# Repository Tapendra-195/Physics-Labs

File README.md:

# Physics-Labs
Contains files related to work done as Department Technician at The University of Winnipeg

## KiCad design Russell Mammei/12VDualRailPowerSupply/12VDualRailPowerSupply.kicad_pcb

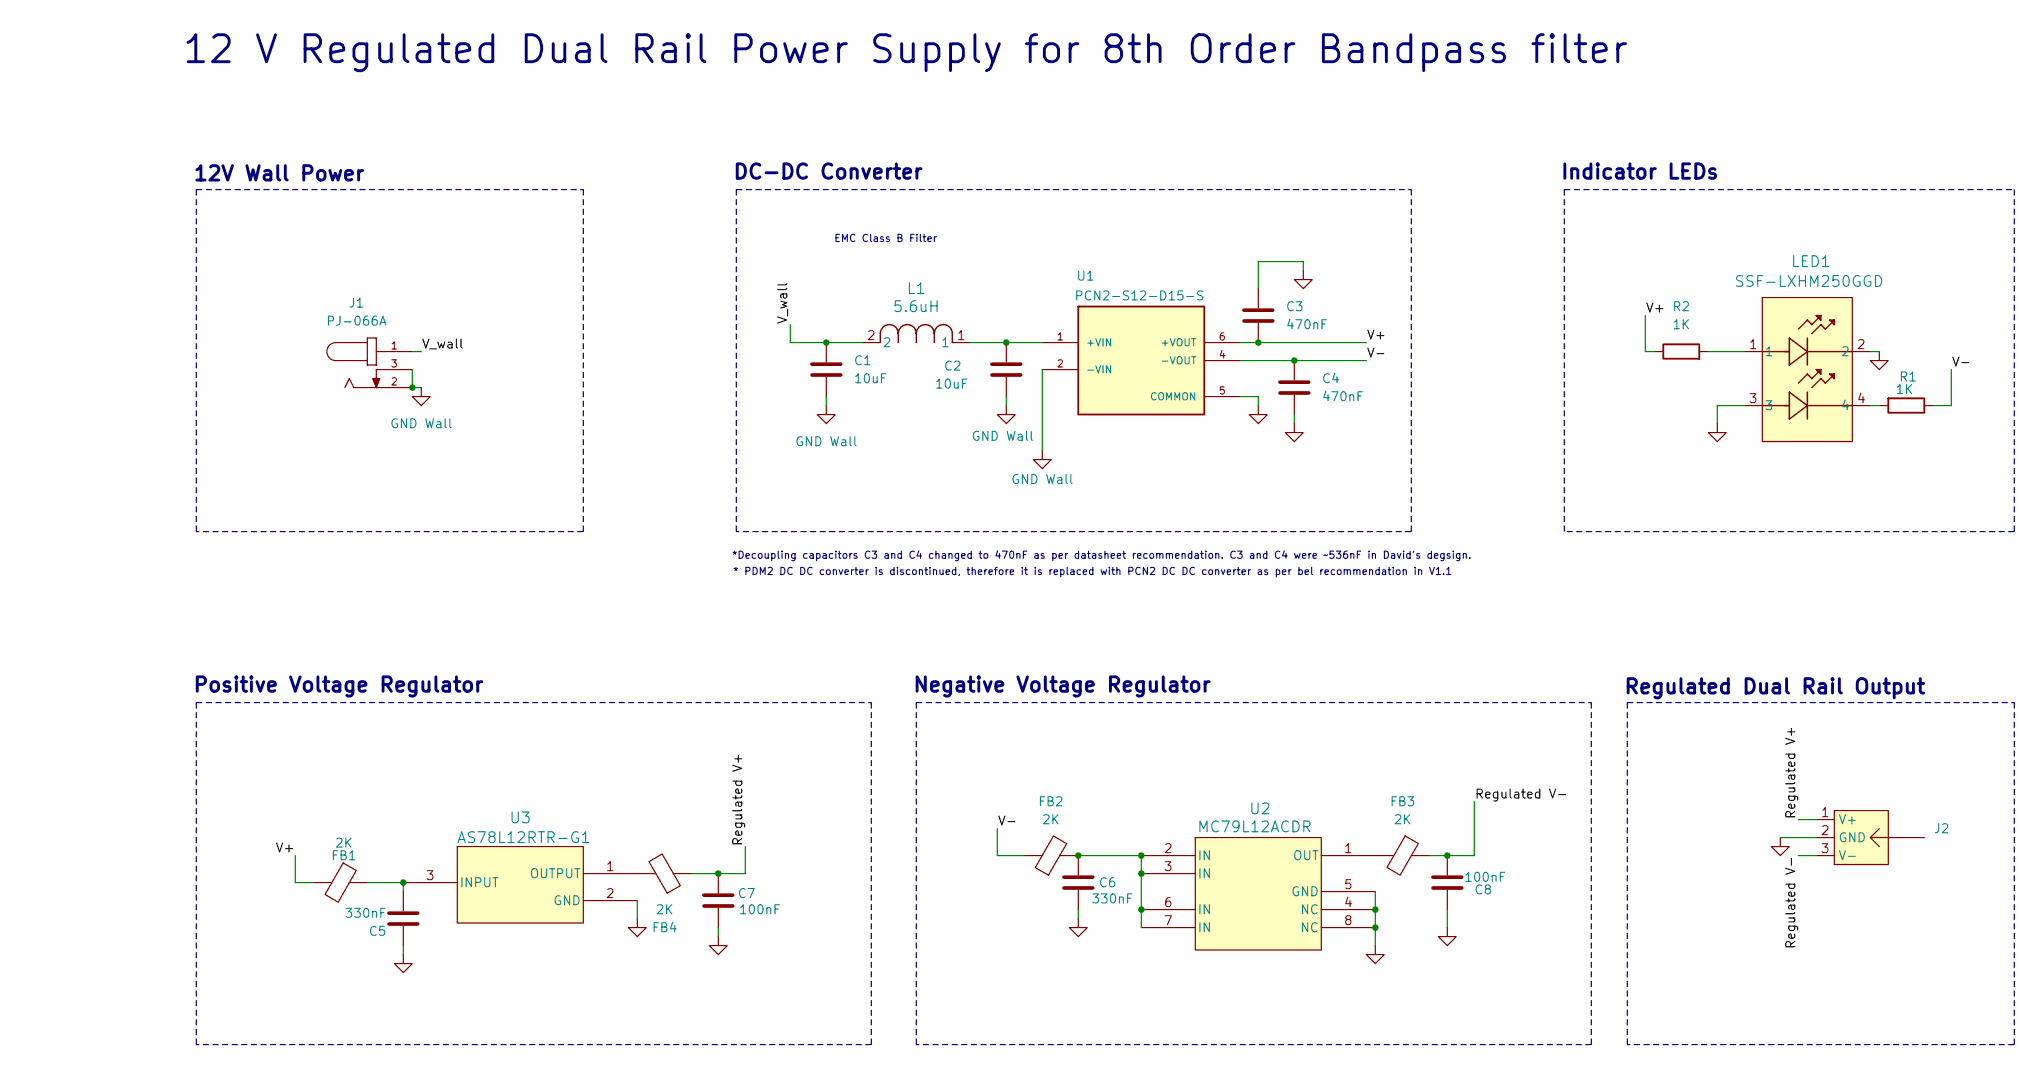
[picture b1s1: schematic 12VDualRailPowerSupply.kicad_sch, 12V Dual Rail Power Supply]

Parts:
C1: 10uF; C_1206_3216Metric_Pad1.33x1.80mm_HandSolder; Part# UMK316AB7475ML-T
C2: 10uF; C_1206_3216Metric_Pad1.33x1.80mm_HandSolder
C3, C4: 470nF; C_0603_1608Metric_Pad1.08x0.95mm_HandSolder
C5, C6: 330nF; C_0805_2012Metric_Pad1.18x1.45mm_HandSolder
C7, C8: 100nF; C_0603_1608Metric_Pad1.08x0.95mm_HandSolder
FB1, FB2, FB3, FB4: 2K; L_0603_1608Metric_Pad1.05x0.95mm_HandSolder; Part# MMZ1608S202ATD25
J1: PJ-066A; CUI_PJ-066A; PARTREV 1.02
J2: 2SH-C-03-TR
L1: 5.6uH; IND_SRN3015BTA-2R2M_BRN-L
LED1: SSF-LXHM250GGD; SSF-LXHM250IGIGW_LUM
R1, R2: 1K; R_1206_3216Metric_Pad1.30x1.75mm_HandSolder
U1: PCN2-S12-D15-S; CONV_PCN2-S12-D15-S; PARTREV 1.0
U2: MC79L12ACDR; D8
U3: AS78L12RTR-G1; SOT-89_DIO

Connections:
/Regulated V+: C7.1, FB4.1, J2.1 (V+)
/Regulated V-: C8.1, FB3.1, J2.3 (V-)
/V+: C3.2, FB1.2, R2.1, U1.6 (+VOUT)
/V-: C4.1, FB2.1, R1.1, U1.4 (-VOUT)
/V_wall: C1.1, J1.1, L1.2
GND: C3.1, C4.2, C5.1, C6.2, C7.2, C8.2, J2.2 (GND), LED1.2, LED1.3, U1.5 (COMMON), U2.4 (NC), U2.5 (GND), U2.8 (NC), U3.2 (GND)
GND Wall: C1.2, C2.2, J1.2, J1.3, U1.2 (-VIN)
unnamed: C6.1, FB2.2, U2.2 (IN), U2.3 (IN), U2.6 (IN), U2.7 (IN)
unnamed: LED1.1, R2.2
unnamed: LED1.4, R1.2
unnamed: C2.1, L1.1, U1.1 (+VIN)
unnamed: FB3.2, U2.1 (OUT)
unnamed: C5.2, FB1.1, U3.3 (INPUT)
unnamed: FB4.2, U3.1 (OUTPUT)

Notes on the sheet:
*Decoupling capacitors C3 and C4 changed to 470nF as per datasheet recommendation. C3 and C4 were ~536nF in David's degsign.
Negative Voltage Regulator
DC-DC Converter
Indicator LEDs
12 V Regulated Dual Rail Power Supply for 8th Order Bandpass filter
Regulated Dual Rail Output
Positive Voltage Regulator
12V Wall Power
EMC Class B Filter
* PDM2 DC DC converter is discontinued, therefore it is replaced with PCN2 DC DC converter as per bel recommendation in V1.1

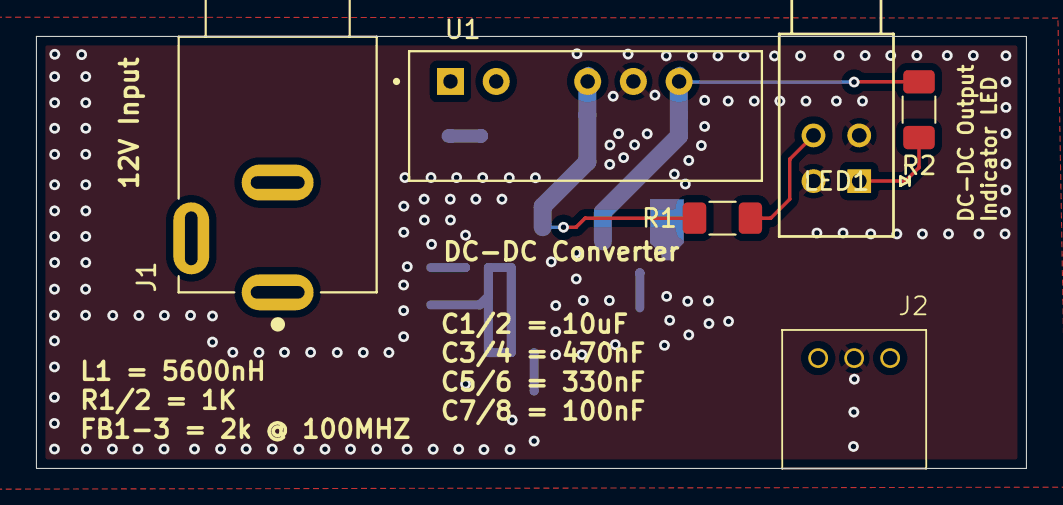
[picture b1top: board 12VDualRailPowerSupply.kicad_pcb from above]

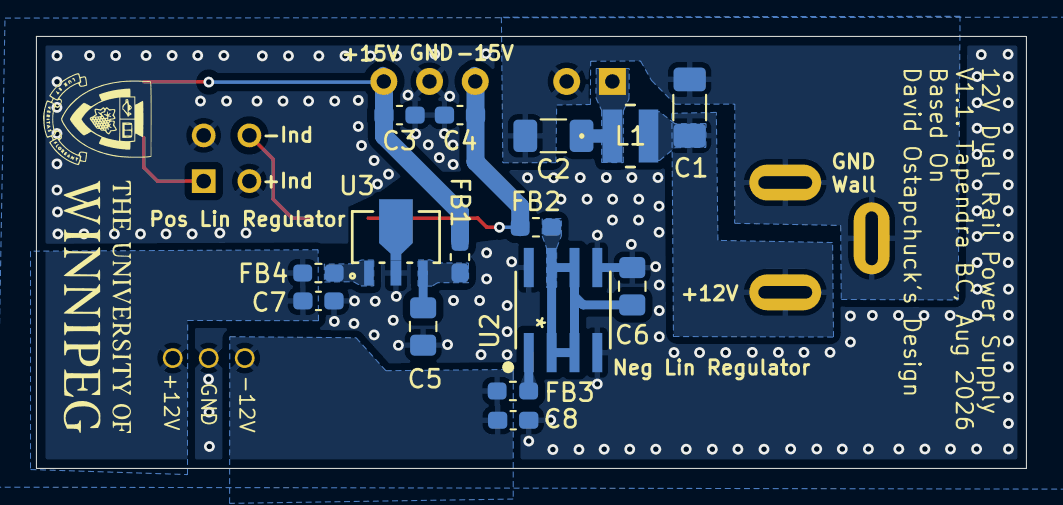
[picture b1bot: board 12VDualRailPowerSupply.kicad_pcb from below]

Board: 4 copper layers, 55.0 x 24.0 mm, 21 parts (15 on the bottom side), 14 nets.

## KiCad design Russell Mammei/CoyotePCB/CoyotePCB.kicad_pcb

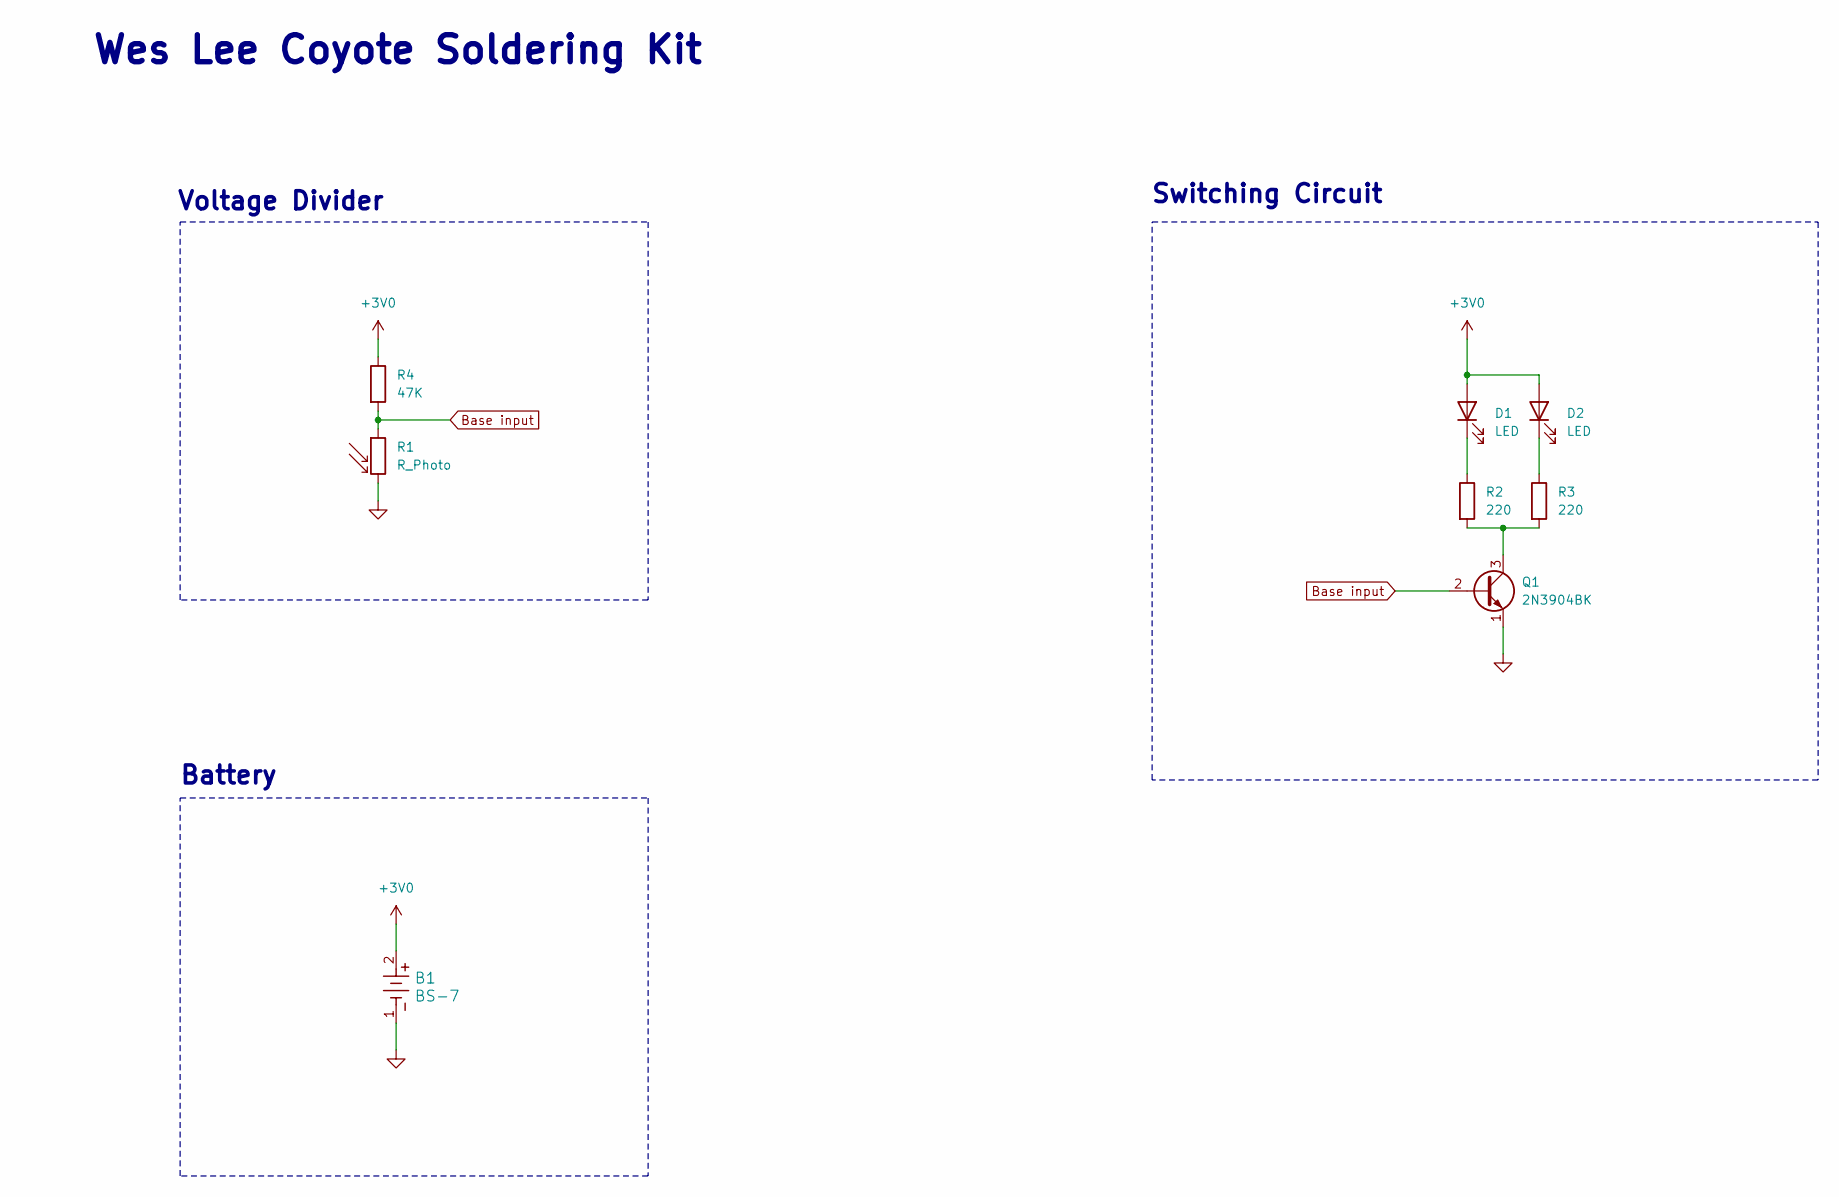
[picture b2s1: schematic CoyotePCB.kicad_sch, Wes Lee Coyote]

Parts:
B1: BS-7; BS-7_MPD
D1, D2: LED; LED_D5.0mm
Q1: 2N3904BK; TO-92_Inline
R1: R_Photo; R_LDR_5.1x4.3mm_P3.4mm_Vertical
R2, R3: 220; R_Axial_DIN0207_L6.3mm_D2.5mm_P10.16mm_Horizontal
R4: 47K; R_Axial_DIN0207_L6.3mm_D2.5mm_P7.62mm_Horizontal

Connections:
+3V0: B1.2, D1.2 (A), D2.2 (A), R4.1
Base input: Q1.2 (B), R1.1, R4.2
GND: B1.1, Q1.1 (E), R1.2
unnamed: D1.1 (K), R2.1
unnamed: D2.1 (K), R3.1
unnamed: Q1.3 (C), R2.2, R3.2

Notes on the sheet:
Voltage Divider
Switching Circuit
Battery
Wes Lee Coyote Soldering Kit

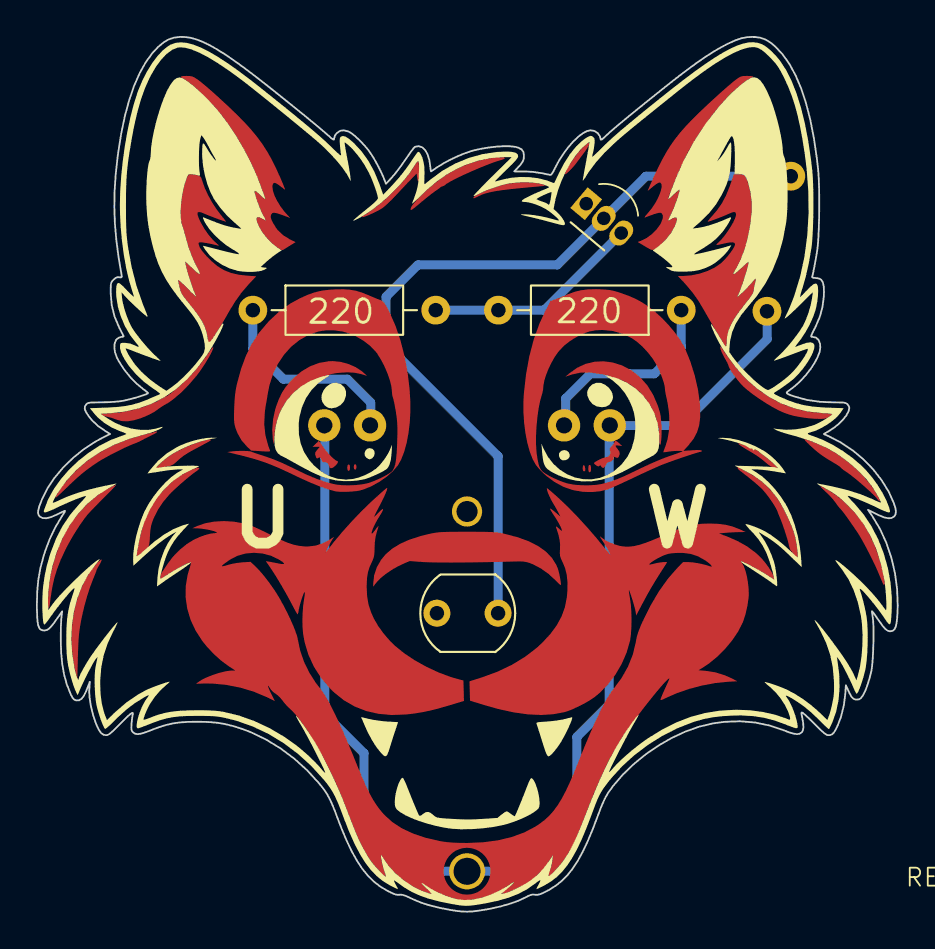
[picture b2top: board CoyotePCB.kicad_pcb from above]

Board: 2 copper layers, 47.8 x 48.6 mm, 8 parts (1 on the bottom side), 6 nets.

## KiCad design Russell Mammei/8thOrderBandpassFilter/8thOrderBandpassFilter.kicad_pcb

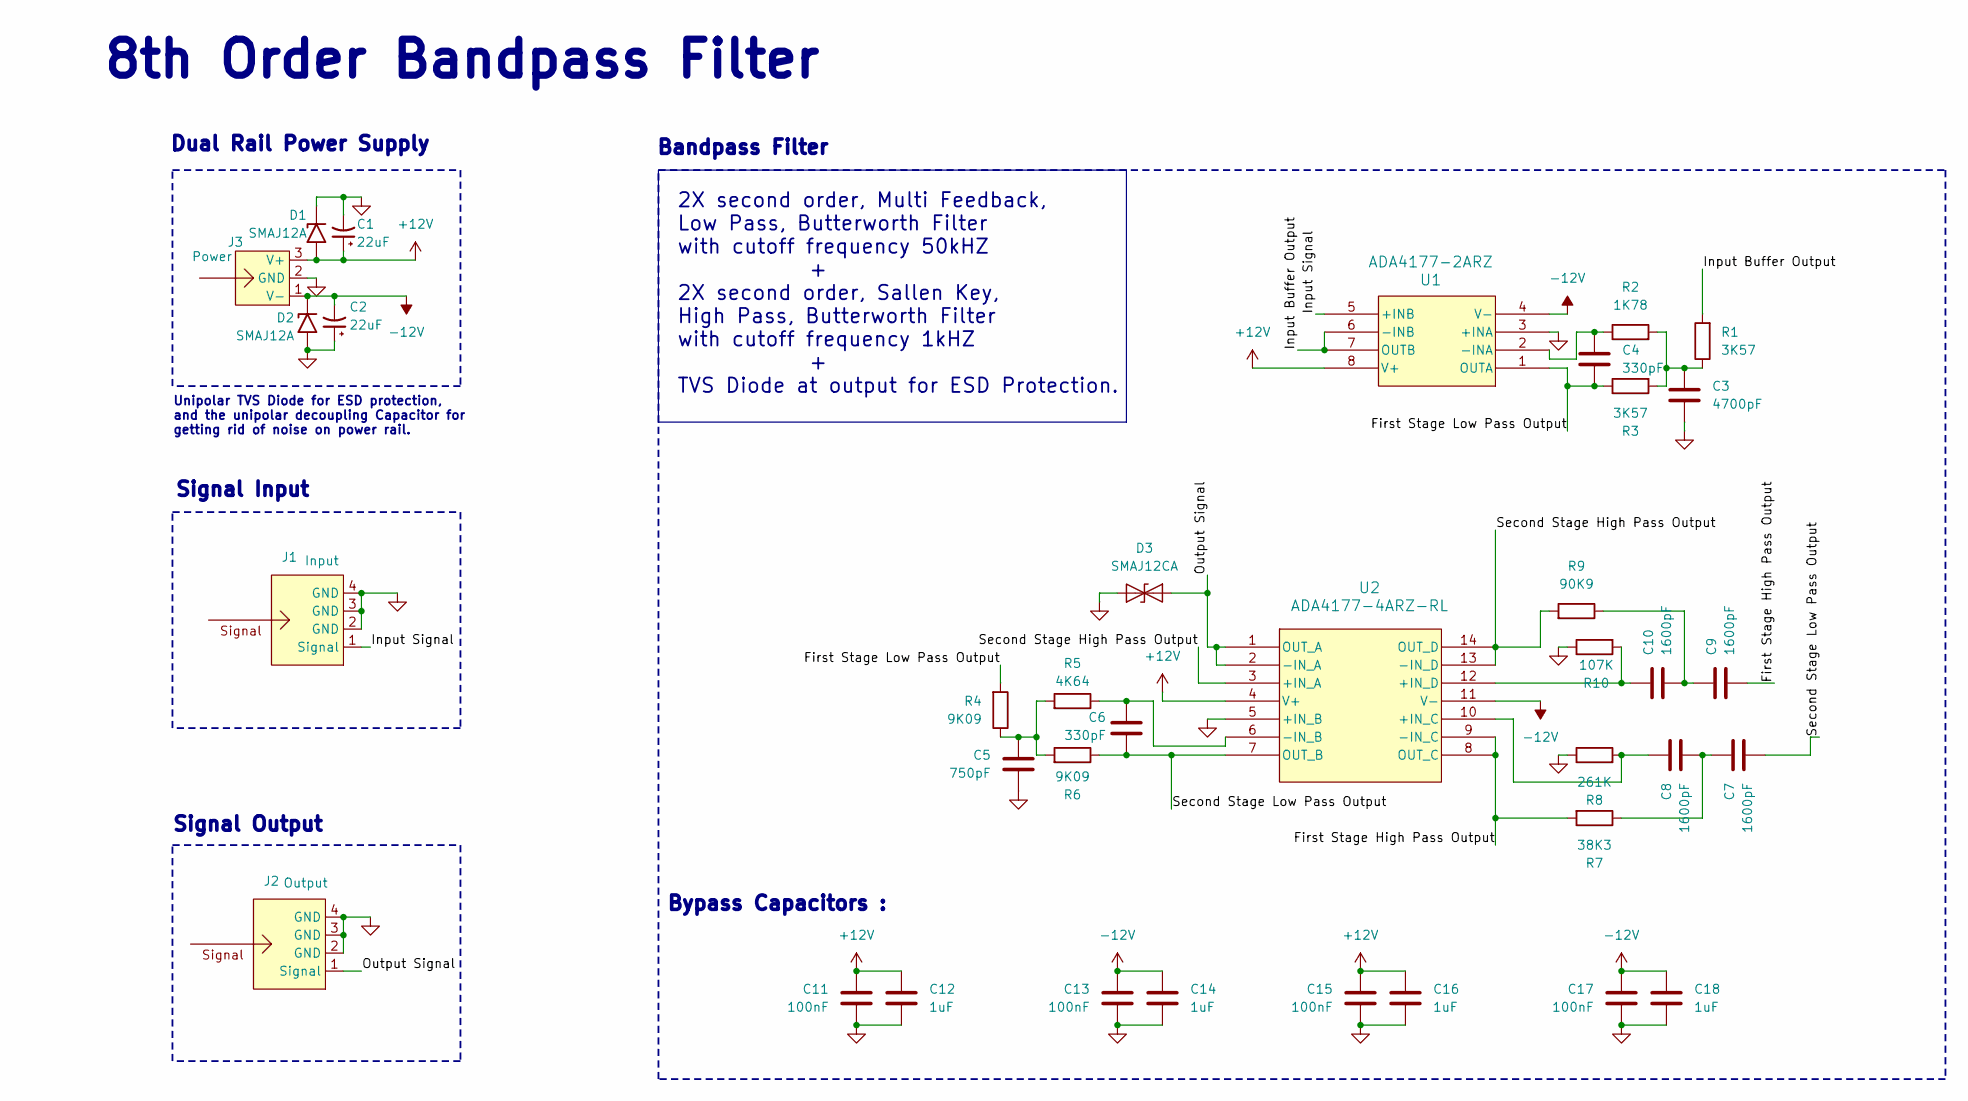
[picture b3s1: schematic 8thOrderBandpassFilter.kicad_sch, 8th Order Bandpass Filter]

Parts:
C1, C2: 22uF; CP_EIA-3216-10_Kemet-I_HandSolder
C3: 4700pF; C_0603_1608Metric_Pad1.08x0.95mm_HandSolder
C4, C6: 330pF; C_0603_1608Metric_Pad1.08x0.95mm_HandSolder
C5: 750pF; C_0603_1608Metric_Pad1.08x0.95mm_HandSolder
C7, C8, C9, C10: 1600pF; C_0603_1608Metric_Pad1.08x0.95mm_HandSolder
C11, C13, C15, C17: 100nF; C_0603_1608Metric_Pad1.08x0.95mm_HandSolder
C12, C14, C16, C18: 1uF; C_0603_1608Metric_Pad1.08x0.95mm_HandSolder
D1, D2: SMAJ12A; D_SMA
D3: SMAJ12CA; D_SMA
J1: Input; 031-5640
J2: Output; 031-5640
J3: Power; 2SH-C-03-TR
R1, R3: 3K57; R_0603_1608Metric_Pad0.98x0.95mm_HandSolder
R2: 1K78; R_0603_1608Metric_Pad0.98x0.95mm_HandSolder
R4, R6: 9K09; R_0603_1608Metric_Pad0.98x0.95mm_HandSolder
R5: 4K64; R_0603_1608Metric_Pad0.98x0.95mm_HandSolder
R7: 38K3; R_0603_1608Metric_Pad0.98x0.95mm_HandSolder
R8: 261K; R_0603_1608Metric_Pad0.98x0.95mm_HandSolder
R9: 90K9; R_0603_1608Metric_Pad0.98x0.95mm_HandSolder
R10: 107K; R_0603_1608Metric_Pad0.98x0.95mm_HandSolder
U1: ADA4177-2ARZ; R_8_ADI
U2: ADA4177-4ARZ-RL; R_14_ADI

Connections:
+12V: C1.1, C11.1, C12.1, C15.1, C16.1, D1.2 (A2), J3.3 (V+), U1.8 (V+), U2.4 (V+)
-12V: C2.2, C13.1, C14.1, C17.1, C18.1, D2.1 (A1), J3.1 (V-), U1.4 (V-), U2.11 (V-)
/First Stage High Pass Output: C9.2, R7.2, U2.8 (OUT_C), U2.9 (-IN_C)
/First Stage Low Pass Output: C4.2, R3.1, R4.2, U1.1 (OUTA)
/Input Buffer Output: R1.2, U1.6 (-INB), U1.7 (OUTB)
/Input Signal: J1.1 (Signal), U1.5 (+INB)
/Output Signal: D3.1 (A1), J2.1 (Signal), U2.1 (OUT_A), U2.2 (-IN_A)
/Second Stage High Pass Output: R9.2, U2.3 (+IN_A), U2.13 (-IN_D), U2.14 (OUT_D)
/Second Stage Low Pass Output: C6.2, C7.2, R6.1, U2.7 (OUT_B)
GND: C1.2, C2.1, C3.2, C5.2, C11.2, C12.2, C13.2, C14.2, C15.2, C16.2, C17.2, C18.2, D1.1 (A1), D2.2 (A2), D3.2 (A2), J1.2 (GND), J1.3 (GND), J1.4 (GND), J2.2 (GND), J2.3 (GND), J2.4 (GND), J3.2 (GND), R8.1, R10.1, U1.3 (+INA), U2.5 (+IN_B)
unnamed: C3.1, R1.1, R2.2, R3.2
unnamed: C5.1, R4.1, R5.2, R6.2
unnamed: C7.1, C8.2, R7.1
unnamed: C9.1, C10.2, R9.1
unnamed: C4.1, R2.1, U1.2 (-INA)
unnamed: C8.1, R8.2, U2.10 (+IN_C)
unnamed: C10.1, R10.2, U2.12 (+IN_D)
unnamed: C6.1, R5.1, U2.6 (-IN_B)

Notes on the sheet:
Bandpass Filter
2X second order, Multi Feedback, Low Pass, Butterworth Filter with cutoff frequency 50kHZ + 2X second order, Sallen Key, High Pass, Butterworth Filter with cutoff frequency 1kHZ + TVS Diode at output for ESD Protection.
Unipolar TVS Diode for ESD protection, and the unipolar decoupling Capacitor for getting rid of noise on power rail.
8th Order Bandpass Filter
Signal Output
Dual Rail Power Supply
Bypass Capacitors :
Signal Input

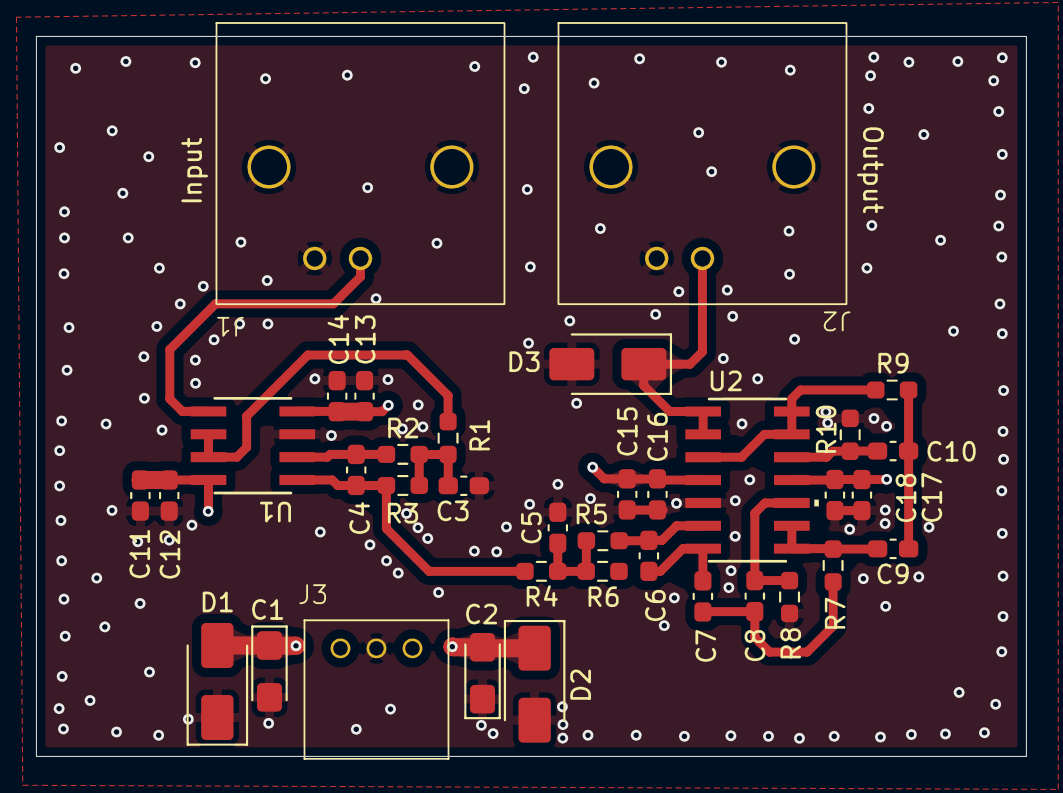
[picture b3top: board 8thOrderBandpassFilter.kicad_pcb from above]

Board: 4 copper layers, 55.0 x 40.0 mm, 36 parts (0 on the bottom side), 18 nets.

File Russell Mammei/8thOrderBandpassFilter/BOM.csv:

"Id";"Designator";"Footprint";"Quantity";"Designation";"Supplier and ref";
1;"C5";"C_0603_1608Metric_Pad1.08x0.95mm_HandSolder";1;"750pF";;;
2;"C1,C2";"CP_EIA-3216-10_Kemet-I_HandSolder";2;"22uF";;;
3;"C18,C16,C14,C12";"C_0603_1608Metric_Pad1.08x0.95mm_HandSolder";4;"1uF";;;
4;"R1,R3";"R_0603_1608Metric_Pad0.98x0.95mm_HandSolder";2;"3K57";;;
5;"R2";"R_0603_1608Metric_Pad0.98x0.95mm_HandSolder";1;"1K78";;;
6;"C9,C8,C10,C7";"C_0603_1608Metric_Pad1.08x0.95mm_HandSolder";4;"1600pF";;;
7;"J2";"031-5640";1;"Output";;;
8;"D2,D1";"D_SMA";2;"SMAJ12A";;;
9;"U2";"R_14_ADI";1;"ADA4177-4ARZ-RL";;;
10;"C13,C17,C11,C15";"C_0603_1608Metric_Pad1.08x0.95mm_HandSolder";4;"100nF";;;
11;"J1";"031-5640";1;"Input";;;
12;"R4,R6";"R_0603_1608Metric_Pad0.98x0.95mm_HandSolder";2;"9K09";;;
13;"R9";"R_0603_1608Metric_Pad0.98x0.95mm_HandSolder";1;"90K9";;;
14;"J3";"2SH-C-03-TR";1;"Power";;;
15;"C4,C6";"C_0603_1608Metric_Pad1.08x0.95mm_HandSolder";2;"330pF";;;
16;"R10";"R_0603_1608Metric_Pad0.98x0.95mm_HandSolder";1;"107K";;;
17;"U1";"R_8_ADI";1;"ADA4177-2ARZ";;;
18;"C3";"C_0603_1608Metric_Pad1.08x0.95mm_HandSolder";1;"4700pF";;;
19;"R5";"R_0603_1608Metric_Pad0.98x0.95mm_HandSolder";1;"4K64";;;
20;"R7";"R_0603_1608Metric_Pad0.98x0.95mm_HandSolder";1;"38K3";;;
21;"R8";"R_0603_1608Metric_Pad0.98x0.95mm_HandSolder";1;"261K";;;
22;"D3";"D_SMA";1;"SMAJ12CA";;;

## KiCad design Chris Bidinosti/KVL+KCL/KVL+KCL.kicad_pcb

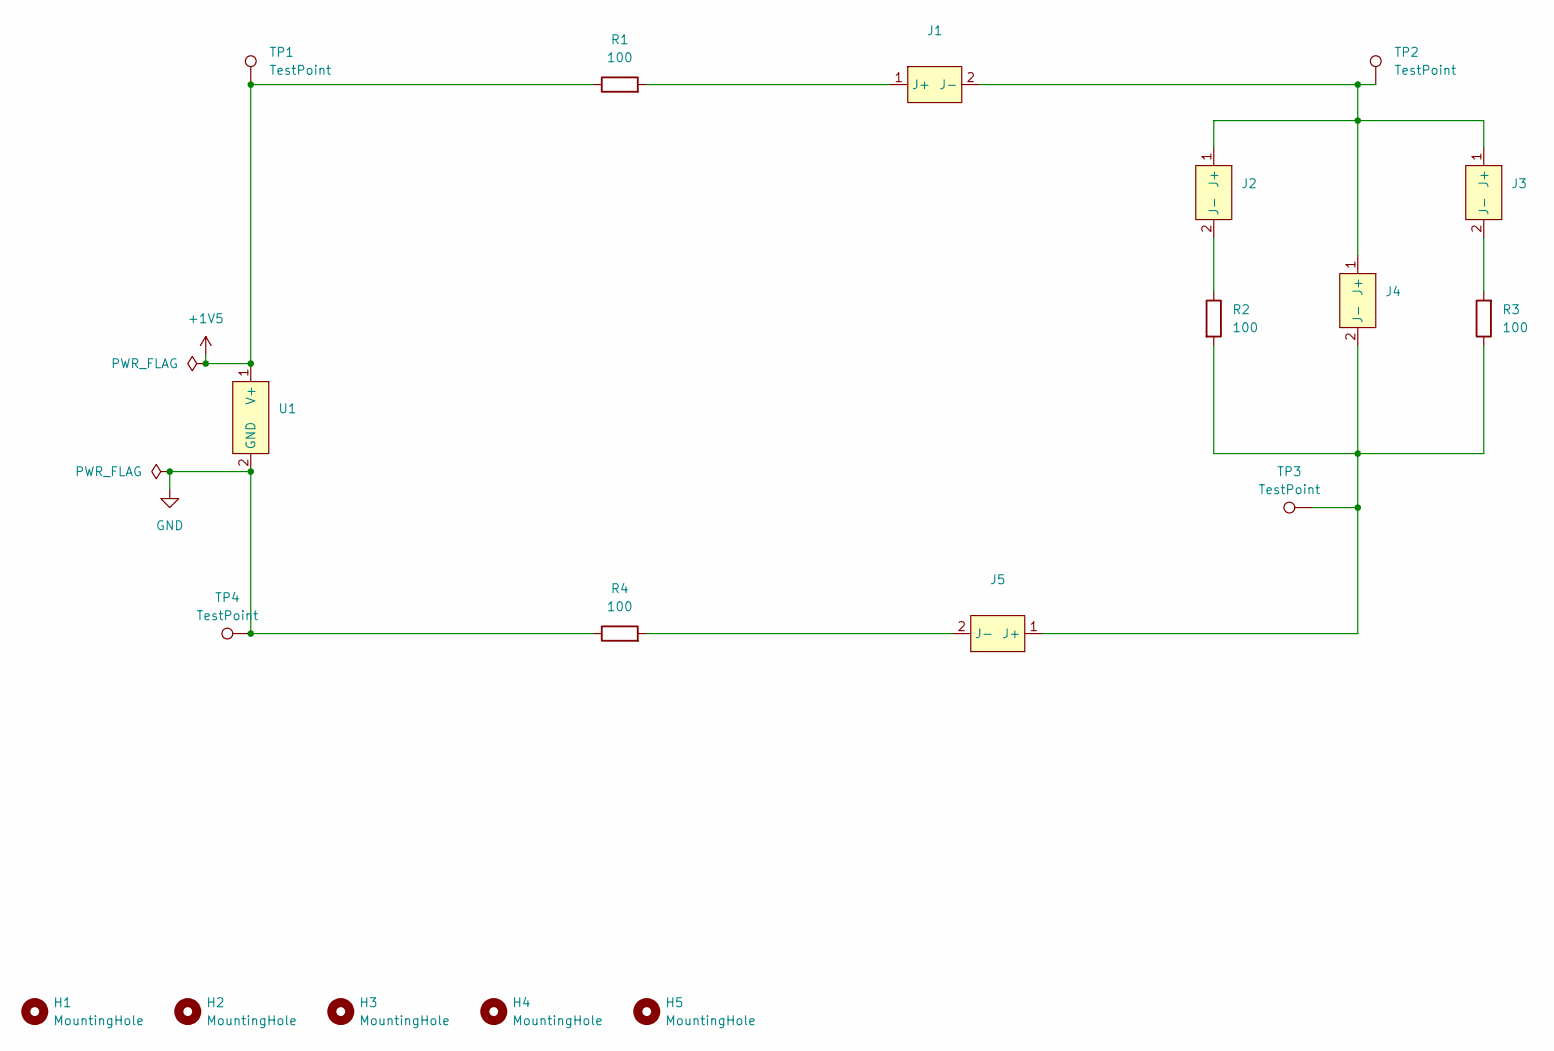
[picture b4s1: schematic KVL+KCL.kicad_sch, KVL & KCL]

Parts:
H1, H2, H3, H4, H5: MountingHole; MountingHole_3.2mm_M3
J1, J2, J3, J4, J5: JumperConnector
R1, R2, R3, R4: 100; R_Axial_DIN0309_L9.0mm_D3.2mm_P12.70mm_Horizontal
TP1, TP2, TP3, TP4: TestPoint; TestPoint_Pad_D2.5mm
U1: power_connector

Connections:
+1V5: R1.1, TP1.1, U1.1 (V+)
GND: R4.1, TP4.1, U1.2 (GND)
unnamed: J1.1 (J+), R1.2
unnamed: J1.2 (J-), J2.1 (J+), J3.1 (J+), J4.1 (J+), TP2.1
unnamed: J2.2 (J-), R2.1
unnamed: J3.2 (J-), R3.2
unnamed: J4.2 (J-), J5.1 (J+), R2.2, R3.1, TP3.1
unnamed: J5.2 (J-), R4.2

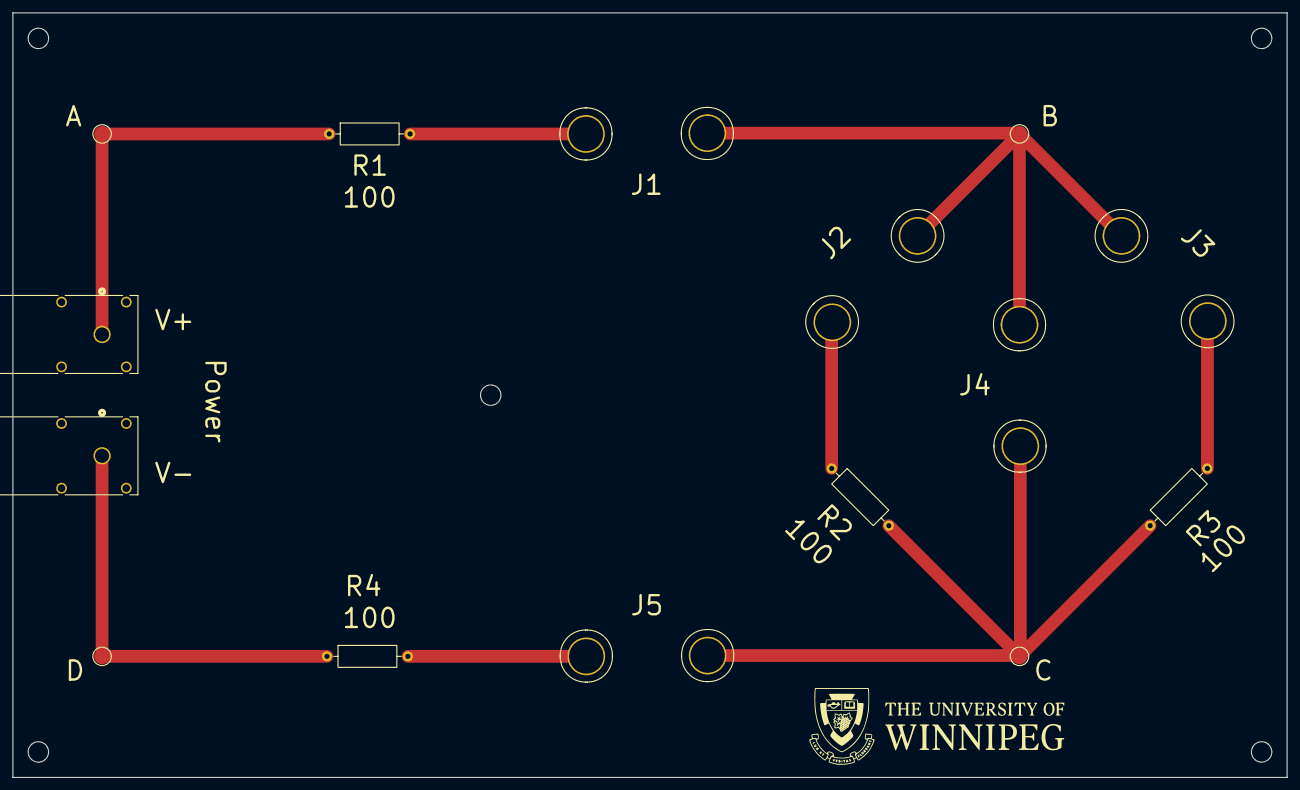
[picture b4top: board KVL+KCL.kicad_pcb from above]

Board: 2 copper layers, 200.0 x 120.0 mm, 19 parts (0 on the bottom side), 8 nets.

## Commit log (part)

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2026-01-08 Split cylinder shims
    Split cylindrical shim set used to adapt a small-diameter round eyepiece for mounting inside an oversized lens tube slip ring, providing concentric alignment and radial spacing.
2026-01-08 Inertia Kit
    Modeled and printed Inertia Kit for Vesna
2026-01-09 Reduced clarence
2026-01-20 KVL+KCL pcb v1
2026-04-28 Modix Big 60 printer files
    Modix Big 60 configuration file, Firmware and doc containing information on 3D printer commissioning.
2026-06-20 3 Axis class demo
    XYZ axis Printed with different colors that is used in teaching classes. The axes snap together using magnet.
